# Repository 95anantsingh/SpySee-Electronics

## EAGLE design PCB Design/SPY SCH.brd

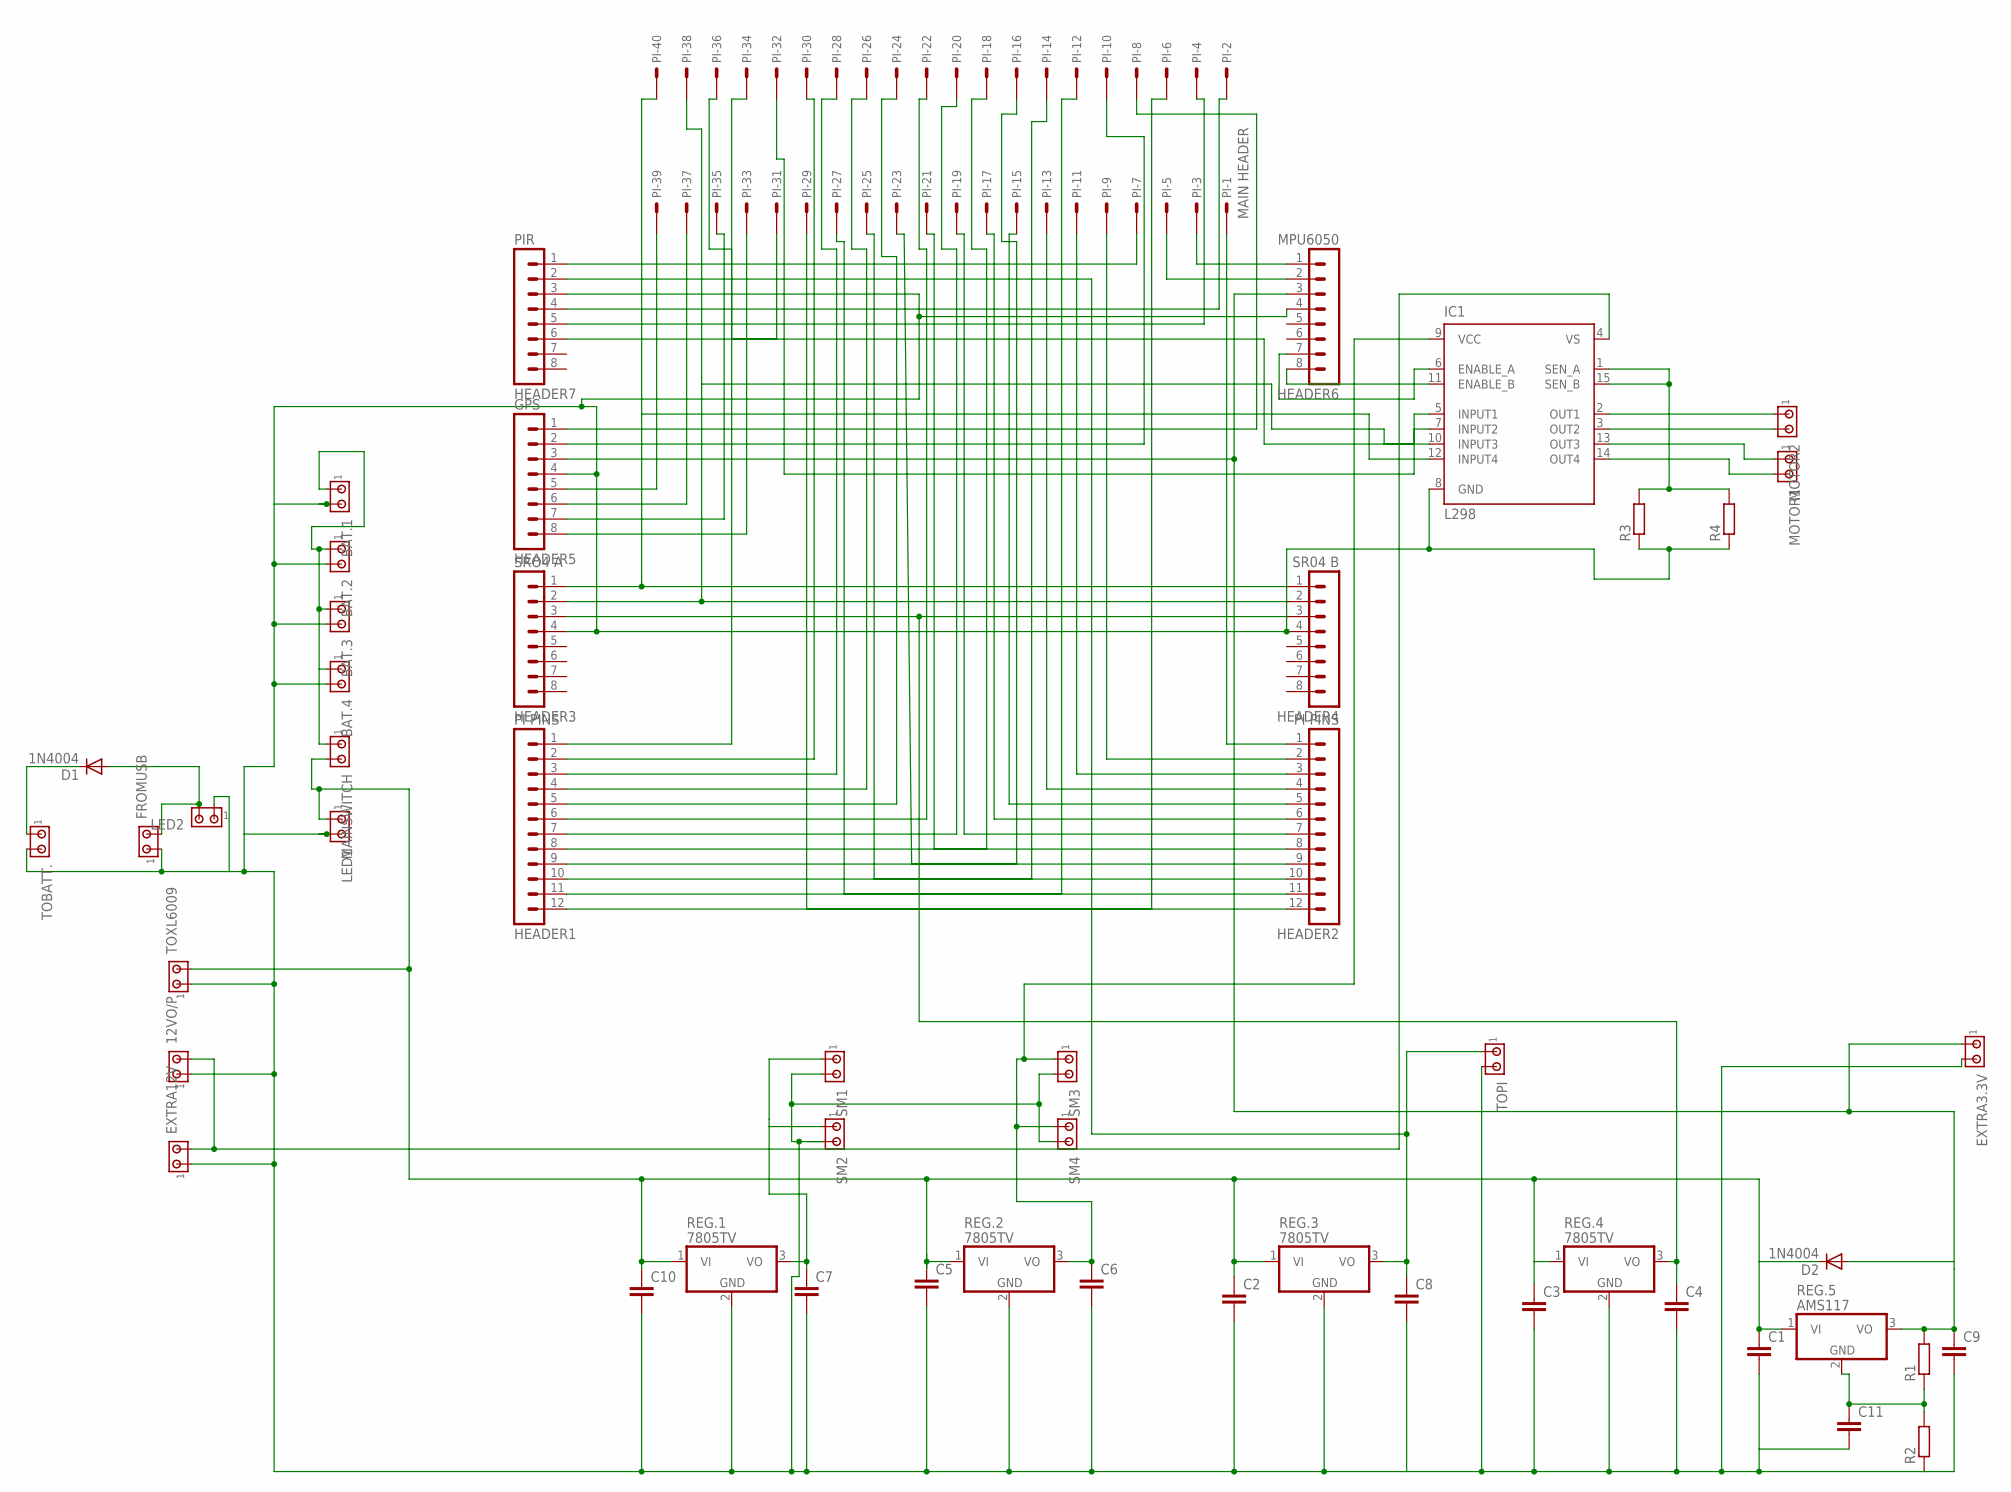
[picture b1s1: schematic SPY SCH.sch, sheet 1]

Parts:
12VO/P: MTA02-156; 1X2MTA
BAT.1, BAT.2, BAT.3, BAT.4: MTA02-156; 1X2MTA
C1, C2, C3, C4, C5, C6, C7, C8, C9, C10, C11: C2,5-3; C2.5-3
D1, D2: 1N4004; DO41-10
EXTRA3.3V, EXTRA12V: MTA02-156; 1X2MTA
FROMUSB: MTA02-156; 1X2MTA
HEADER1, HEADER2: PI PINS; MA12-1W
HEADER3: SRO4 A; MA08-1
HEADER4: SR04 B; MA08-1
HEADER5: GPS; MA08-1
HEADER6: MPU6050; MA08-1
HEADER7: PIR; MA08-1
IC1: L298; MULTIWATT-15
LED1, LED2: MTA02-156; 1X2MTA
MAINSWITCH: MTA02-156; 1X2MTA
MOTOR1, MOTOR2: MTA02-156; 1X2MTA
PI: MAIN HEADER; 057-040-1
R1, R2, R3, R4: R-EU_0309/12; 0309/12
REG.1, REG.2, REG.3, REG.4: 7805TV; TO220V
REG.5: AMS117; TO220V
SM1, SM2, SM3, SM4: MTA02-156; 1X2MTA
TOBATT.: MTA02-156; 1X2MTA
TOPI: MTA02-156; 1X2MTA
TOXL6009: MTA02-156; 1X2MTA

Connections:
unnamed: HEADER7.1, PI.7
unnamed: HEADER7.4, PI.2
unnamed: D1.C, TOBATT..1
unnamed: D1.A, FROMUSB.2, LED2.2
unnamed: HEADER5.1, PI.8
unnamed: HEADER6.2, PI.5
unnamed: C8.1, HEADER7.2, REG.3.3 (VO), TOPI.1
unnamed: C6.1, IC1.9 (VCC), REG.2.3 (VO), SM3.1, SM4.1
unnamed: HEADER5.2, PI.10
unnamed: HEADER3.2, HEADER4.2, IC1.10 (INPUT3), PI.38
unnamed: IC1.7 (INPUT2), PI.36
unnamed: HEADER3.1, HEADER4.1, IC1.12 (INPUT4), PI.40
unnamed: HEADER6.1, PI.3
unnamed: C1.1, C2.1, C3.1, C5.1, C10.1, D2.C, LED1.1, MAINSWITCH.2, REG.1.1 (VI), REG.2.1 (VI), REG.3.1 (VI), REG.4.1 (VI), REG.5.1 (VI), TOXL6009.2
unnamed: BAT.1.1, BAT.2.1, BAT.3.1, BAT.4.1, MAINSWITCH.1
unnamed: C9.1, D2.A, EXTRA3.3V.1, HEADER5.3, HEADER6.3, R1.2, REG.5.3 (VO)
unnamed: HEADER1.1, PI.34
unnamed: C4.1, HEADER3.3, HEADER4.3, REG.4.3 (VO)
unnamed: C7.1, REG.1.3 (VO), SM1.1, SM2.1
unnamed: IC1.5 (INPUT1), PI.32
unnamed: 12VO/P.2, EXTRA12V.2, IC1.4 (VS)
unnamed: HEADER1.7, PI.20
unnamed: HEADER1.2, PI.30
unnamed: HEADER1.3, PI.28
unnamed: HEADER1.4, PI.26
unnamed: HEADER1.5, PI.24
unnamed: HEADER1.6, PI.22
unnamed: HEADER1.8, PI.18
unnamed: HEADER1.9, PI.16
unnamed: HEADER1.10, PI.14
unnamed: HEADER1.11, PI.12
unnamed: HEADER1.12, PI.6
unnamed: HEADER2.1, PI.1
unnamed: HEADER2.2, PI.9
unnamed: HEADER2.3, PI.11
unnamed: HEADER2.4, PI.13
unnamed: HEADER2.5, PI.15
unnamed: HEADER2.7, PI.19
unnamed: HEADER2.8, PI.21
unnamed: HEADER2.9, PI.23
unnamed: HEADER2.6, PI.17
unnamed: HEADER2.10, PI.25
unnamed: HEADER2.11, PI.27
unnamed: HEADER2.12, PI.29
unnamed: HEADER7.5, PI.4
unnamed: HEADER6.8, IC1.11 (ENABLE_B)
unnamed: HEADER7.6, PI.31
unnamed: HEADER5.5, PI.39
unnamed: HEADER5.6, PI.37
unnamed: HEADER5.7, PI.35
unnamed: HEADER5.8, PI.33
unnamed: C11.1, R1.1, R2.2, REG.5.2 (GND)
unnamed: 12VO/P.1, BAT.1.2, BAT.2.2, BAT.3.2, BAT.4.2, C1.2, C2.2, C3.2, C4.2, C5.2, C6.2, C7.2, C8.2, C9.2, C10.2, C11.2, EXTRA3.3V.2, EXTRA12V.1, FROMUSB.1, HEADER3.4, HEADER4.4, HEADER5.4, HEADER6.4, HEADER7.3, IC1.8 (GND), LED1.2, LED2.1, R2.1, R3.1, R4.1, REG.1.2 (GND), REG.2.2 (GND), REG.3.2 (GND), REG.4.2 (GND), SM1.2, SM2.2, SM3.2, SM4.2, TOBATT..2, TOPI.2, TOXL6009.1
unnamed: IC1.1 (SEN_A), IC1.15 (SEN_B), R3.2, R4.2
unnamed: IC1.2 (OUT1), MOTOR2.1
unnamed: IC1.3 (OUT2), MOTOR2.2
unnamed: IC1.13 (OUT3), MOTOR1.1
unnamed: IC1.14 (OUT4), MOTOR1.2
unnamed: HEADER6.7, IC1.6 (ENABLE_A)

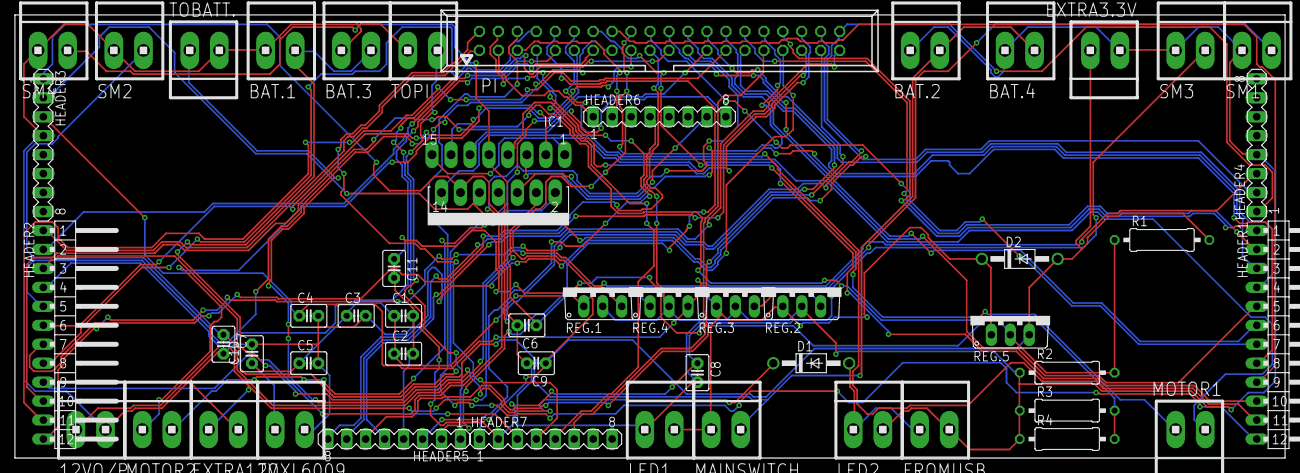
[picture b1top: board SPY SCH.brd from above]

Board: 2 copper layers, 170.2 x 59.4 mm, 51 parts (0 on the bottom side), 59 nets.
